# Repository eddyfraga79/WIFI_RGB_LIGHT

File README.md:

# WIFI_RGB_LIGHT
An RGB light powered by USB and controlled via WIFI using an embedded webserver

* Make sure to set the transmit terminal configuration to: LF
  * Used to configure the device via USB terminal for SSID, PASSWORD and NAME configuraations
  * This was tested using Tera Term

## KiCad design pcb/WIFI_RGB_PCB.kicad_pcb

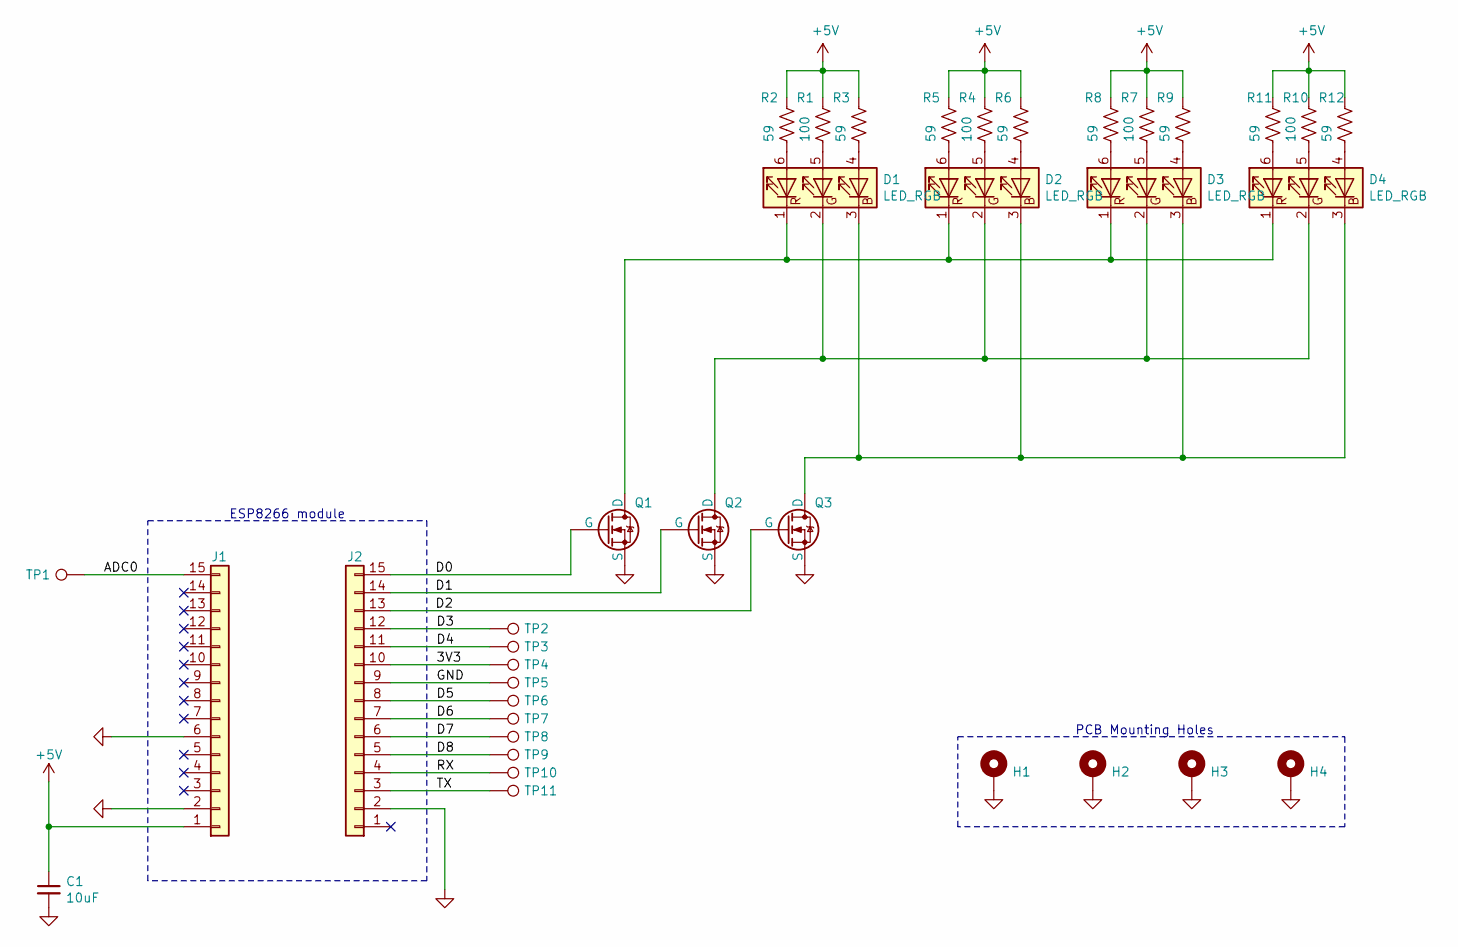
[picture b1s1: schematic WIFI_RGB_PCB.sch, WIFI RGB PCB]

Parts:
C1: 10uF; C_1206_3216Metric
D1, D2, D3, D4: LED_RGB; LED_WS2812_PLCC6_5.0x5.0mm_P1.6mm
H1, H2, H3, H4: MountingHole_Pad; MountingHole_2.2mm_M2_Pad
J1, J2: Conn_01x15; PinHeader_1x15_P2.54mm_Vertical
Q1, Q2, Q3: Q_ZXMN3A03E6; SOT-23-6_Handsoldering
R1, R4, R7, R10: 100; R_0805_2012Metric
R2, R3, R5, R6, R8, R9, R11, R12: 59; R_0805_2012Metric
TP1, TP2, TP3, TP4, TP5, TP6, TP7, TP8, TP9, TP10, TP11: TestPoint; TestPoint_THTPad_2.5x2.5mm_Drill1.2mm

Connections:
+5V: C1.1, J1.1, R1.1, R2.1, R3.1, R4.1, R5.1, R6.1, R7.1, R8.1, R9.1, R10.1, R11.1, R12.1
/3V3: J2.10, TP4.1
/ADC0: J1.15, TP1.1
/D0: J2.15, Q1.3 (G)
/D1: J2.14, Q2.3 (G)
/D2: J2.13, Q3.3 (G)
/D3: J2.12, TP2.1
/D4: J2.11, TP3.1
/D5: J2.8, TP6.1
/D6: J2.7, TP7.1
/D7: J2.6, TP8.1
/D8: J2.5, TP9.1
/RX: J2.4, TP10.1
/TX: J2.3, TP11.1
GND: C1.2, H1.1, H2.1, H3.1, H4.1, J1.2, J1.6, J2.2, J2.9, Q1.4 (S), Q2.4 (S), Q3.4 (S), TP5.1
unnamed: D1.1 (RK), D2.1 (RK), D3.1 (RK), D4.1 (RK), Q1.1 (D), Q1.2 (D), Q1.5 (D), Q1.6 (D)
unnamed: D1.2 (GK), D2.2 (GK), D3.2 (GK), D4.2 (GK), Q2.1 (D), Q2.2 (D), Q2.5 (D), Q2.6 (D)
unnamed: D1.3 (BK), D2.3 (BK), D3.3 (BK), D4.3 (BK), Q3.1 (D), Q3.2 (D), Q3.5 (D), Q3.6 (D)
unnamed: D1.4 (BA), R3.2
unnamed: D1.5 (GA), R1.2
unnamed: D1.6 (RA), R2.2
unnamed: D2.4 (BA), R6.2
unnamed: D2.5 (GA), R4.2
unnamed: D2.6 (RA), R5.2
unnamed: D3.4 (BA), R9.2
unnamed: D3.5 (GA), R7.2
unnamed: D3.6 (RA), R8.2
unnamed: D4.4 (BA), R12.2
unnamed: D4.5 (GA), R10.2
unnamed: D4.6 (RA), R11.2

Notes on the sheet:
ESP8266 module
PCB Mounting Holes

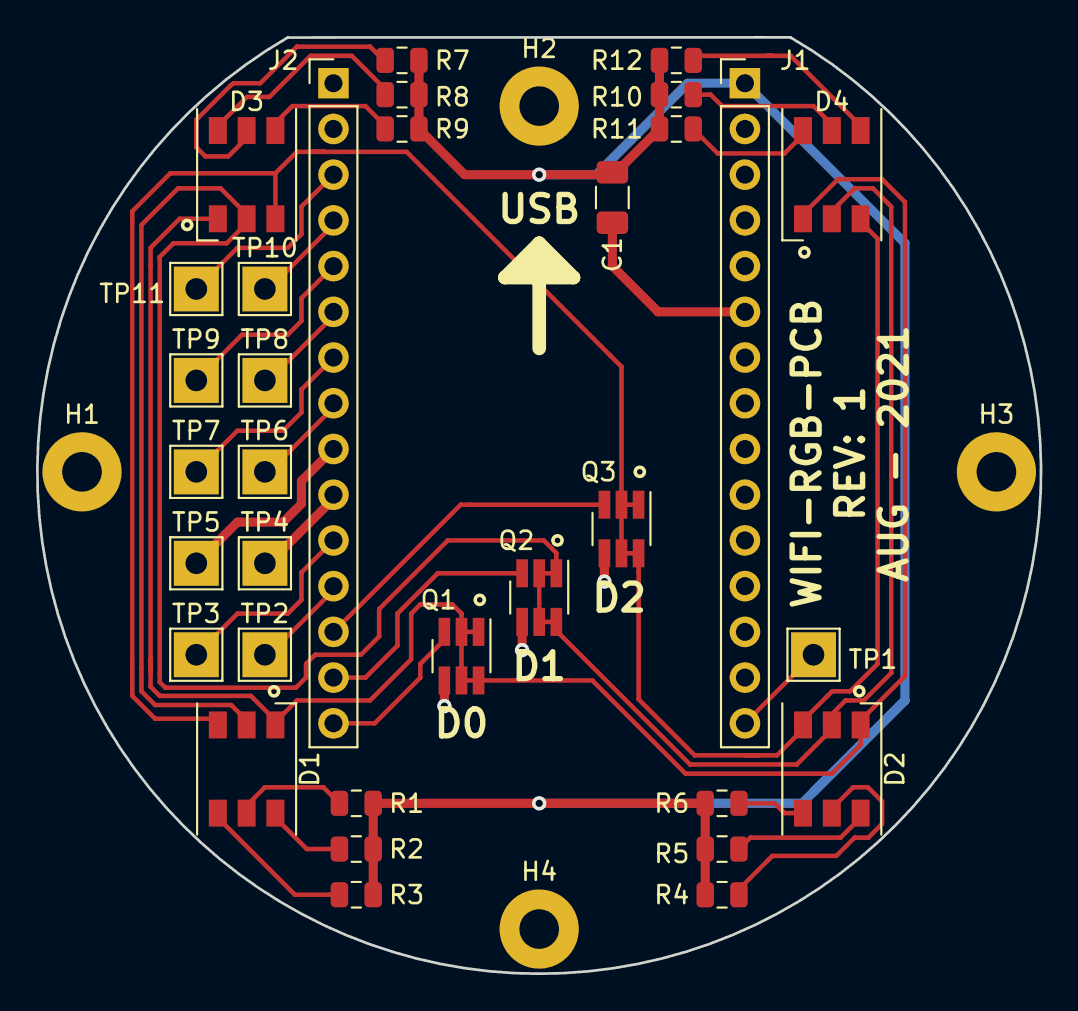
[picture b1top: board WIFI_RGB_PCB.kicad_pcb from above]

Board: 2 copper layers, 55.8 x 52.0 mm, 37 parts (0 on the bottom side), 30 nets.

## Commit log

2022-08-08 Add files via upload
    Schematic file that was forgotten during the first inital upload to GitHub.
2024-10-19 Update README.md
    Updated MEADME file to add some extra details about system configuration via USB
2024-10-19 Update README.md
    Minor correction to the text.
